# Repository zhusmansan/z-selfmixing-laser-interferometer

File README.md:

# Драйвер для лазера и усилитель фотодиода для самосмешиваюей интерферометрии(self-mixing interferometry, [SMI](https://en.wikipedia.org/wiki/Self-mixing_interferometry)).

Воспроизведён эксперимент [Laser diode self-mixing: Range-finding and sub-micron vibration measurement](https://www.youtube.com/watch?v=MUdro-6u2Zg)

## Схема драйвера\усилителя

1) Фильтры питания и стабилизатор 5в
2) Регулируемый источник постоянного тока
3) Трансимпедансный усилитель сигнала фотодиода с регулируемым усилением
4) Дополнительная ступень усиления х10

 Схему для KiCad можно посмотреть в соответствующей [папке](./z-selfmixing-laser-interferometer-kicad/)

Номиналы фильтрующих конденсаторов выбраны при помощи ГПСЧ.

## Печатная плата

Плата односторонняя, произведена методом лазерного экспонирования фоторезиста.

Травление -- 1 флакон перекиси водорода, 20г лимонной кислоты, чайная ложка поваренной соли. Для ускорения травления, раствор подогреть в микроволновой печи.

Питание устройства от 2х 9в батареек. Удобный бесшумный источник питания для весьма чувствительного усилителя.

## Установка

  1) Лазер со встроенным фотодиодом контроля мощности. Использован дешёвый лазер с фокусирующей оптикой типа: 
  Электроника управления лазером удалена, пины лазерного диода и фотодиода выведены наружу, через разъём типа JST_PH(3).

  2) Усилитель запитан от 2 элементов типа крона.

  3) Лазер направлен на мембрану динамика с наклеенной световозвращающей лентой. Динамик приводится в действие генератором сигнала, встроенным в осциллограф.

## Результат

На осцилограмме: зелёная линия -- сигнал подаваемый на динамик, жёлтая линия -- осцилограмма интерферометрического сигнала.

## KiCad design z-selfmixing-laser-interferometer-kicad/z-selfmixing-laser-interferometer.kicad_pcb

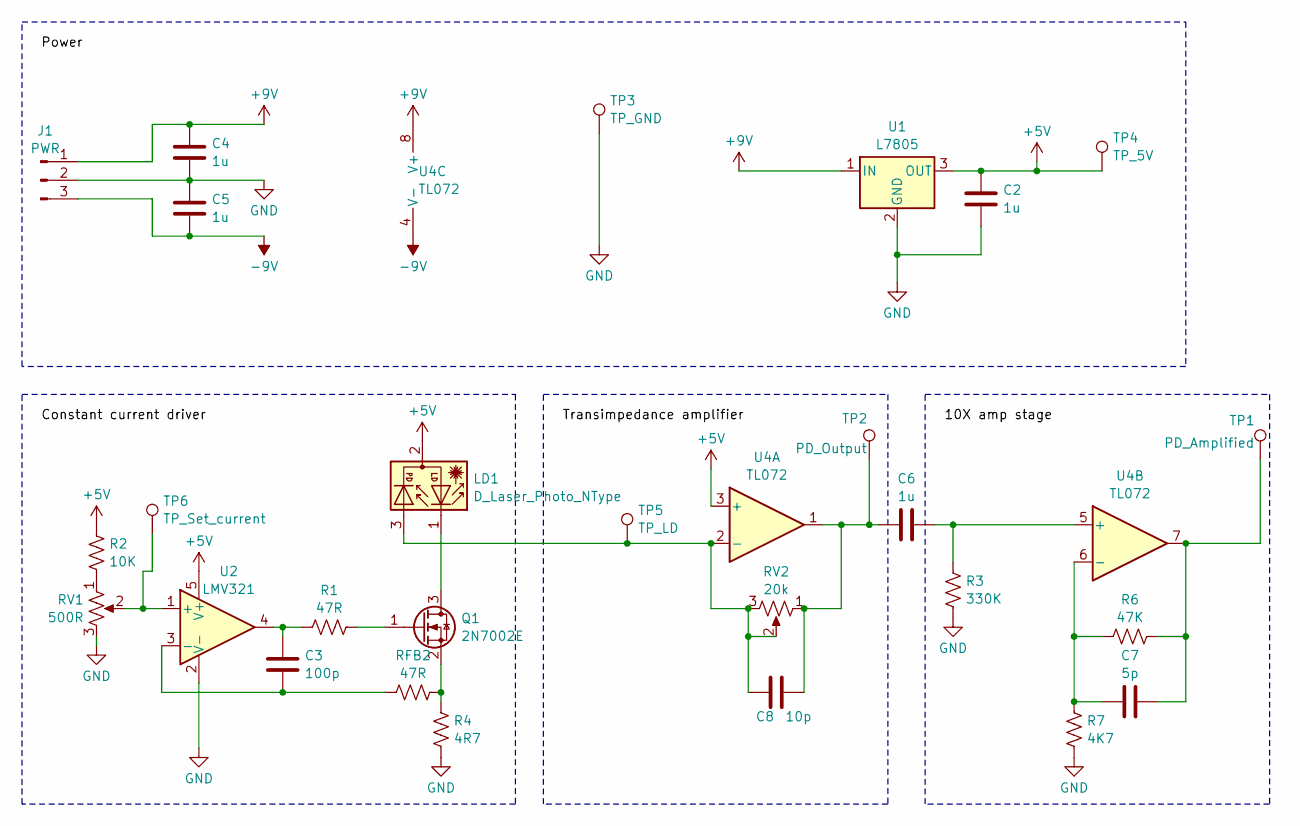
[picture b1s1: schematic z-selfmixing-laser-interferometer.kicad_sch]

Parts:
C2, C4, C5, C6: 1u; C_0805_2012Metric_Pad1.18x1.45mm_HandSolder
C3: 100p; C_0805_2012Metric_Pad1.18x1.45mm_HandSolder
C7: 5p; C_0805_2012Metric_Pad1.18x1.45mm_HandSolder
C8: 10p; C_0805_2012Metric_Pad1.18x1.45mm_HandSolder
J1: PWR; JST_XH_B3B-XH-A_1x03_P2.50mm_Vertical
LD1: D_Laser_Photo_NType; JST_PH_B3B-PH-K_1x03_P2.00mm_Vertical
Q1: 2N7002E; SOT-23
R1: 47R; R_0805_2012Metric_Pad1.20x1.40mm_HandSolder
R2: 10K; R_0805_2012Metric_Pad1.20x1.40mm_HandSolder
R3: 330K; R_0805_2012Metric_Pad1.20x1.40mm_HandSolder
R4: 4R7; R_0805_2012Metric_Pad1.20x1.40mm_HandSolder
R6: 47K; R_0805_2012Metric_Pad1.20x1.40mm_HandSolder
R7: 4K7; R_0805_2012Metric_Pad1.20x1.40mm_HandSolder
RFB2: 47R; R_0805_2012Metric_Pad1.20x1.40mm_HandSolder
RV1: 500R; Potentiometer_Bourns_3296W_Vertical
RV2: 20k; Potentiometer_Bourns_3296W_Vertical
TP1: PD_Amplified; PinHeader_1x01_P2.54mm_Vertical
TP2: PD_Output; PinHeader_1x01_P2.54mm_Vertical
TP3: TP_GND; PinHeader_1x01_P2.54mm_Vertical
TP4: TP_5V; PinHeader_1x01_P2.54mm_Vertical
TP5: TP_LD; PinHeader_1x01_P2.54mm_Vertical
TP6: TP_Set_current; PinHeader_1x01_P2.54mm_Vertical
U1: L7805; TO-252-2
U2: LMV321; SOT-23-5_HandSoldering
U4: TL072; SO-8_3.9x4.9mm_P1.27mm

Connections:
+5V: C2.1, LD1.2, R2.1, TP4.1, U1.3 (OUT), U2.5 (V+), U4.3 (+)
+9V: C4.1, J1.1, U1.1 (IN), U4.8 (V+)
-9V: C5.2, J1.3, U4.4 (V-)
GND: C2.2, C4.2, C5.1, J1.2, R3.2, R4.2, R7.2, RV1.3, TP3.1, U1.2 (GND), U2.2 (V-)
unnamed: C3.1, R1.1, U2.4
unnamed: C6.1, C8.2, RV2.1, TP2.1, U4.1
unnamed: C7.2, R6.2, TP1.1, U4.7
unnamed: LD1.1, Q1.3 (D)
unnamed: Q1.1 (G), R1.2
unnamed: Q1.2 (S), R4.1, RFB2.1
unnamed: R2.2, RV1.1
unnamed: RV1.2, TP6.1, U2.1 (+)
unnamed: C3.2, RFB2.2, U2.3 (-)
unnamed: C8.1, LD1.3, RV2.2, RV2.3, TP5.1, U4.2 (-)
unnamed: C6.2, R3.1, U4.5 (+)
unnamed: C7.1, R6.1, R7.1, U4.6 (-)

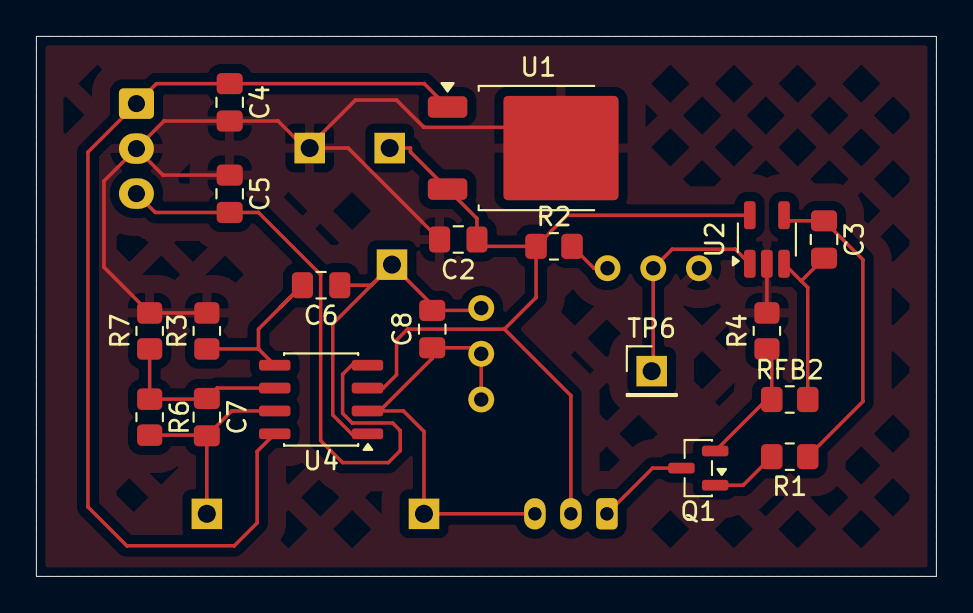
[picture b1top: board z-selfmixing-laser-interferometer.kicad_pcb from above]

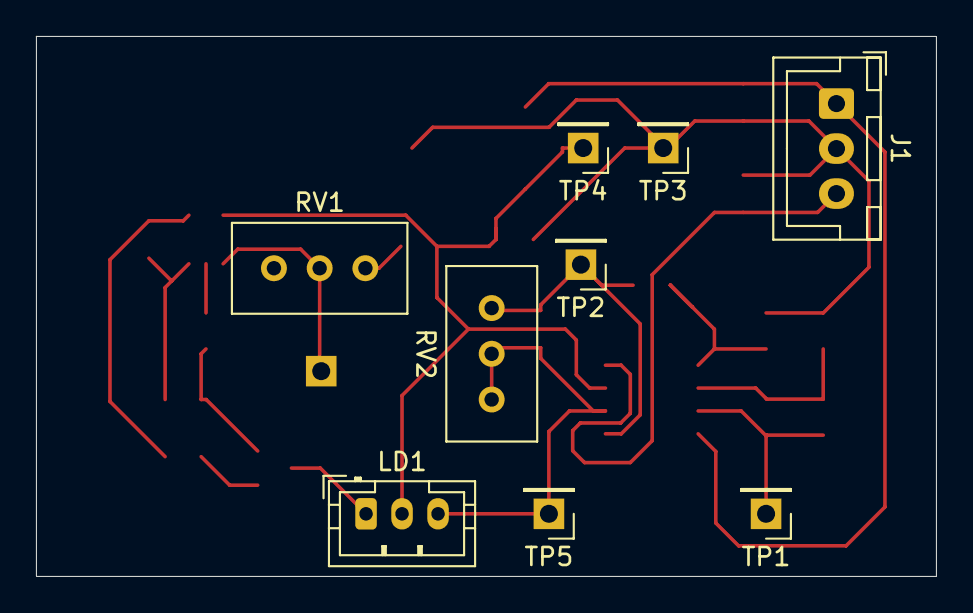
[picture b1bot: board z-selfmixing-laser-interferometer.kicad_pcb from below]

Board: 2 copper layers, 50.0 x 30.0 mm, 28 parts (9 on the bottom side), 16 nets.

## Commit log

2025-12-19 Описание проекта
2025-12-19 лишние файлы --
2025-12-19 +гитигнор
